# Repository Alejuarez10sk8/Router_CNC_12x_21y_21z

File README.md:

# Router_CNC_12x_21y_21z
Primer_router_cnc

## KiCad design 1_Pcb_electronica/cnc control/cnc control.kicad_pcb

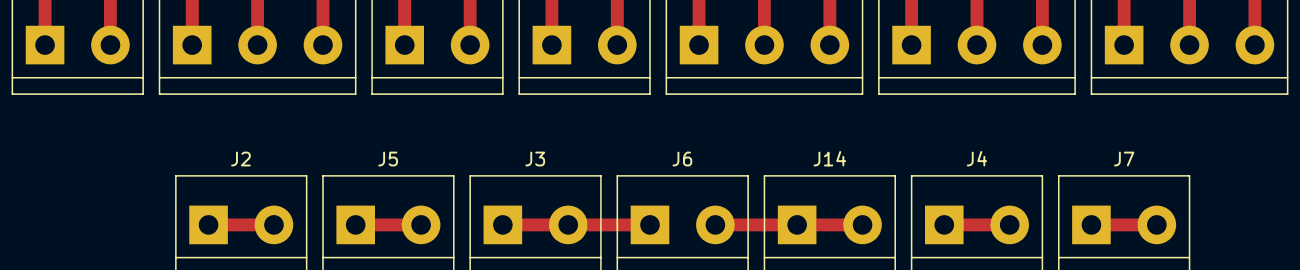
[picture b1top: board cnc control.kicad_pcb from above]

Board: 2 copper layers, 14 parts (0 on the bottom side), 8 nets.

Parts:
J1: Enable+; TerminalBlock_bornier-2_P5.08mm
J2: Pulse X+; TerminalBlock_bornier-2_P5.08mm
J3: Pulse Y+; TerminalBlock_bornier-2_P5.08mm
J4: Pulse Z+; TerminalBlock_bornier-2_P5.08mm
J5: Direction X+; TerminalBlock_bornier-2_P5.08mm
J6: Y+; TerminalBlock_bornier-2_P5.08mm
J7: Direction Z+; TerminalBlock_bornier-2_P5.08mm
J8: PUL -; TerminalBlock_bornier-3_P5.08mm
J9: DIR-; TerminalBlock_bornier-3_P5.08mm
J10: ENA-; TerminalBlock_bornier-3_P5.08mm
J11, J12: Z2; TerminalBlock_bornier-2_P5.08mm
J13: Enable +; TerminalBlock_bornier-3_P5.08mm
J14: Direction Y+; TerminalBlock_bornier-2_P5.08mm

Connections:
unnamed: J1.1, J1.2, J13.1, J13.2, J13.3
unnamed: J2.1, J2.2
unnamed: J3.1, J3.2, J6.1
unnamed: J4.1, J4.2
unnamed: J5.1, J5.2
unnamed: J7.1, J7.2
unnamed: J8.1, J8.2, J8.3, J9.1, J9.2, J9.3, J10.1, J10.2, J10.3, J11.1, J11.2, J12.1, J12.2
unnamed: J6.2, J14.1, J14.2

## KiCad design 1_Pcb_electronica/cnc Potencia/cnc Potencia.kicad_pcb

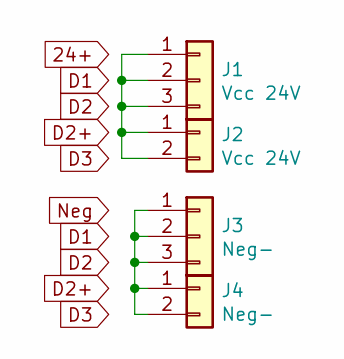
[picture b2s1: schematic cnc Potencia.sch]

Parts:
J1: Vcc 24V; TerminalBlock_bornier-3_P5.08mm
J2: Vcc 24V; TerminalBlock_bornier-2_P5.08mm
J3: Neg-; TerminalBlock_bornier-3_P5.08mm
J4: Neg-; TerminalBlock_bornier-2_P5.08mm

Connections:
unnamed: J1.1, J1.2, J1.3, J2.1, J2.2
unnamed: J3.1, J3.2, J3.3, J4.1, J4.2

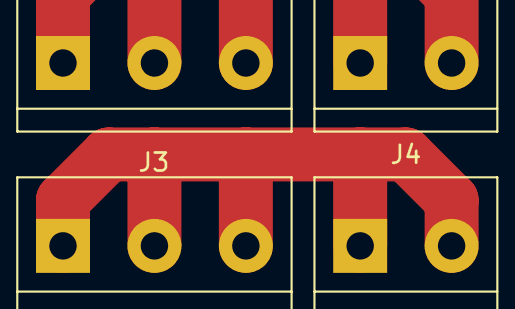
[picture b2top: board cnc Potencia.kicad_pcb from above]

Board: 2 copper layers, 4 parts (0 on the bottom side), 2 nets.
